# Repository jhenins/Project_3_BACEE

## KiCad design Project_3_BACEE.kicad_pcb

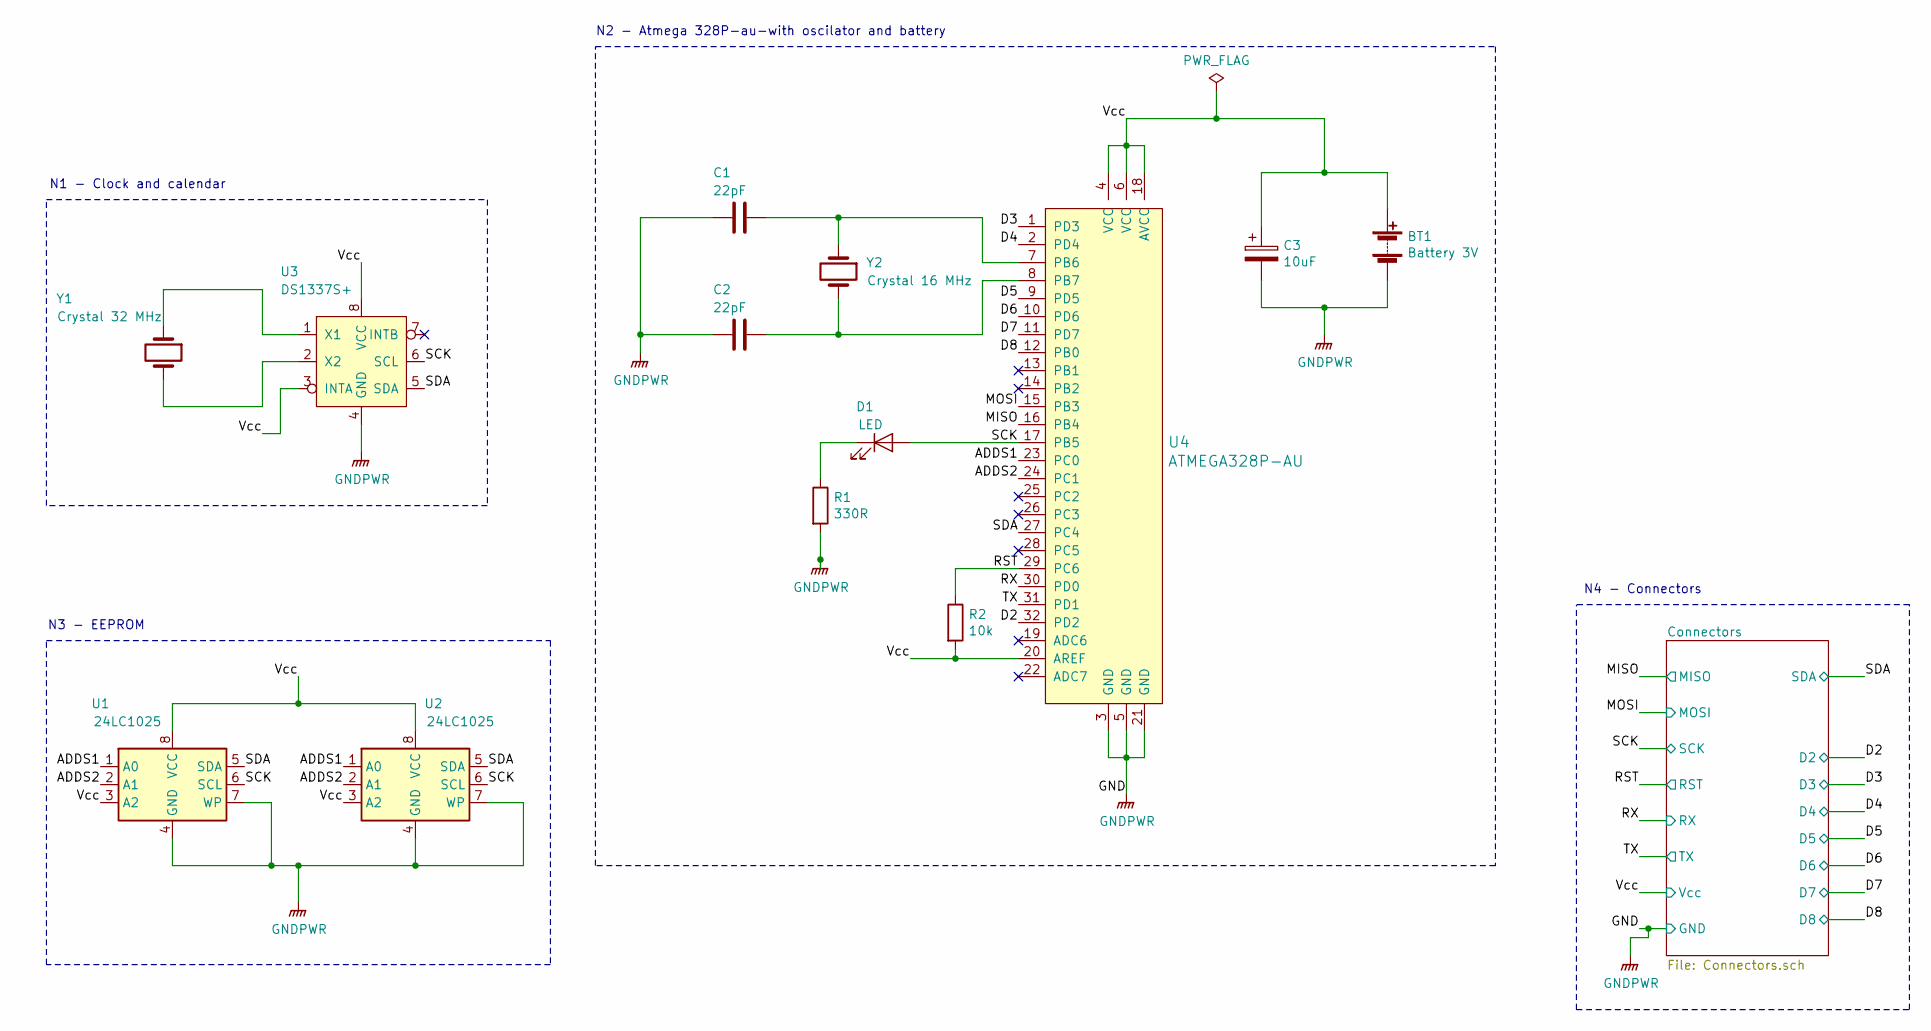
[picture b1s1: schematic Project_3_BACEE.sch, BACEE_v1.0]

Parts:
BT1: Battery 3V; PinHeader_1x02_P2.54mm_Vertical
C1, C2: 22pF; C_0805_2012Metric_Pad1.15x1.40mm_HandSolder
C3: 10uF; C_0805_2012Metric_Pad1.15x1.40mm_HandSolder
D1: LED; LED_0805_2012Metric_Pad1.15x1.40mm_HandSolder
R1: 330R; R_0805_2012Metric_Pad1.15x1.40mm_HandSolder
R2: 10k; R_0805_2012Metric_Pad1.15x1.40mm_HandSolder
U1, U2: 24LC1025; SOIJ-8_5.3x5.3mm_P1.27mm
U3: DS1337S+; SO-8_5.3x6.2mm_P1.27mm
U4: ATMEGA328P-AU; TQFP-32_7x7mm; MPN ATMEGA328P-AU; Digi-Key_PN ATMEGA328P-AU-ND
Y1: Crystal 32 MHz; Crystal_SMD_MicroCrystal_CC7V-T1A-2Pin_3.2x1.5mm_HandSolder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
Y2: Crystal 16 MHz; Crystal_SMD_5032-2Pin_5.0x3.2mm_HandSoldering

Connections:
/ADDS1: U1.1 (A0), U2.1 (A0), U4.23 (PC0)
/ADDS2: U1.2 (A1), U2.2 (A1), U4.24 (PC1)
/D2: U4.32 (PD2); also elsewhere on the board
/D3: U4.1 (PD3); also elsewhere on the board
/D4: U4.2 (PD4); also elsewhere on the board
/D5: U4.9 (PD5); also elsewhere on the board
/D6: U4.10 (PD6); also elsewhere on the board
/D7: U4.11 (PD7); also elsewhere on the board
/D8: U4.12 (PB0); also elsewhere on the board
/MISO: U4.16 (PB4); also elsewhere on the board
/MOSI: U4.15 (PB3); also elsewhere on the board
/RST: R2.1, U4.29 (PC6); also elsewhere on the board
/RX: U4.30 (PD0); also elsewhere on the board
/SCK: D1.2 (A), U1.6 (SCL), U2.6 (SCL), U3.6 (SCL), U4.17 (PB5); also elsewhere on the board
/SDA: U1.5 (SDA), U2.5 (SDA), U3.5 (SDA), U4.27 (PC4); also elsewhere on the board
/TX: U4.31 (PD1); also elsewhere on the board
/Vcc: BT1.1 (+), C3.1, R2.2, U1.3 (A2), U1.8 (VCC), U2.3 (A2), U2.8 (VCC), U3.3 (INTA), U3.8 (VCC), U4.4 (VCC), U4.6 (VCC), U4.18 (AVCC), U4.20 (AREF); also elsewhere on the board
GNDPWR: BT1.2 (-), C1.2, C2.2, C3.2, R1.2, U1.4 (GND), U1.7 (WP), U2.4 (GND), U2.7 (WP), U3.4 (GND), U4.3 (GND), U4.5 (GND), U4.21 (GND); also elsewhere on the board
unnamed: C1.1, U4.7 (PB6), Y2.1
unnamed: C2.1, U4.8 (PB7), Y2.2
unnamed: D1.1 (K), R1.1
unnamed: U3.1 (X1), Y1.1
unnamed: U3.2 (X2), Y1.2

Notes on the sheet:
N1 - Clock and calendar
N3 - EEPROM
N2 - Atmega 328P-au-with oscilator and battery
N4 - Connectors

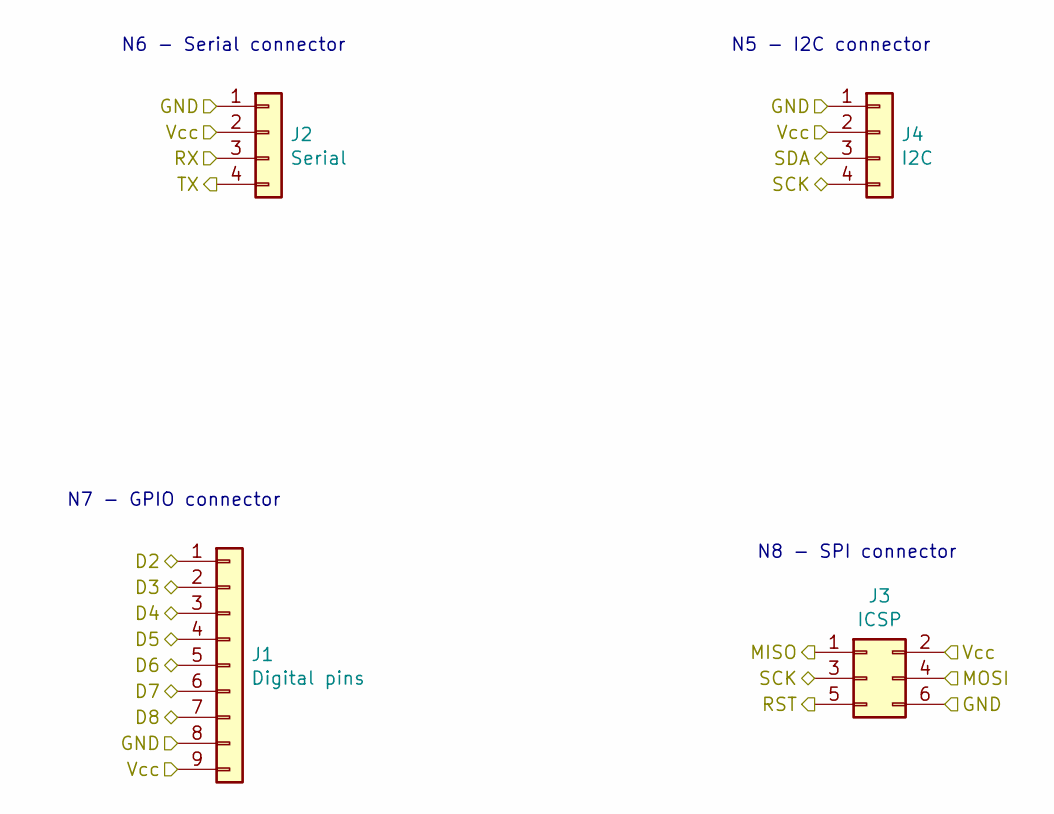
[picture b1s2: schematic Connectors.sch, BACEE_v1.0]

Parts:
J1: Digital pins; PinSocket_1x09_P2.54mm_Vertical
J2: Serial; PinSocket_1x04_P2.54mm_Vertical
J3: ICSP; PinSocket_2x03_P2.54mm_Vertical
J4: I2C; PinSocket_1x04_P2.54mm_Vertical

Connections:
/D2: J1.1; also elsewhere on the board
/D3: J1.2; also elsewhere on the board
/D4: J1.3; also elsewhere on the board
/D5: J1.4; also elsewhere on the board
/D6: J1.5; also elsewhere on the board
/D7: J1.6; also elsewhere on the board
/D8: J1.7; also elsewhere on the board
/MISO: J3.1; also elsewhere on the board
/MOSI: J3.4; also elsewhere on the board
/RST: J3.5; also elsewhere on the board
/RX: J2.3; also elsewhere on the board
/SCK: J3.3, J4.4; also elsewhere on the board
/SDA: J4.3; also elsewhere on the board
/TX: J2.4; also elsewhere on the board
/Vcc: J1.9, J2.2, J3.2, J4.2; also elsewhere on the board
GNDPWR: J1.8, J2.1, J3.6, J4.1; also elsewhere on the board

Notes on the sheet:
N6 - Serial connector
N5 - I2C connector
N7 - GPIO connector
N8 - SPI connector

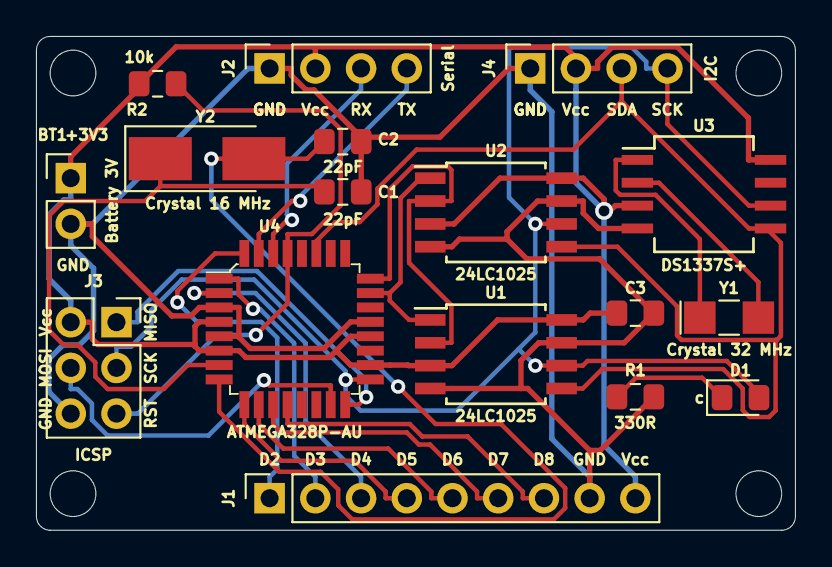
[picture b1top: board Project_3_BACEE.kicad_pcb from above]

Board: 2 copper layers, 42.2 x 27.4 mm, 17 parts (0 on the bottom side), 23 nets.

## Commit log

2019-09-19 First commit.
2019-09-19 Setup the title block in schematic sheet.
2019-09-19 Created new child sheet, added project symbols.
2019-09-19 Added symbol for Atmega328p-au.
2019-09-19 Added costume DS1337 I2C Real Time Clock.
2019-09-19 Added missing crystals.
2019-09-19 Arranged symbols.
2019-09-19 Anottated.
2019-09-19 Added footprints assigments.
2019-09-20 Completed asociations and added component values.
2019-09-20 Completed wiring and connectors sheet.
2019-09-20 COmpleted wiring in root sheet.
2019-09-20 Added power flag symbol.
2019-09-20 Added functional block description.
2019-09-20 Created netlist file.
2019-09-21 Started work in PCBnew.
2019-09-21 Set design rules.
2019-09-21 Placement complete.
2019-09-21 Created outline and mounting holes.
2019-09-21 Fully routed board in two layers.
2019-09-21 Created copper filled area for 2 layer board.
2019-09-21 Completed work in silkscreen.
2019-09-21 Added fully silkscreen and logos.
2019-09-21 Added gerber files for manufacturing.
